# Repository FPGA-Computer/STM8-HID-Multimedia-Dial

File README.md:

# STM8 HID Multimedia Dial

This is a USB HID with a rotatory encoder. This is used to supplement old keyboard layouts by providing a more natural alternative.

Details: https://hw-by-design.blogspot.com/2018/07/hid-multimedia-dial.html

This is a port of my [HID Dial project](https://github.com/FPGA-Computer/HID-Multimedia-Dial) (ATMega8) to STM8S003 using STM8 VUSB library.

# STM8 VUSB

The firmware only USB stack is an unofficial fork from STM8S-VUSB-KEYBOARD at https://github.com/BBS215/STM8S-VUSB-KEYBOARD

- Works with current special edition of Cosmic C (4.4.10) and current version of STVD (4.3.12)

- USB stack logic is modified for this tech demo. HID is now working.

- Code reformatted/refractored.  Using my own IRQ files for STM8S003 for a much cleaner organization. Some code logic changed.

- No longer need a separate GPIO for the 1.5K pull up to connect/disconnect USB.  See schematic.

- Device library calls have been changed to bare metal to minimized dependancy and reduce code size.  stm8s_flash.c is the only library needed.

Note: 

The USB stack calibrates the HSI clock while connected to the PC. The calibration is store in EEPROM. It can take a couple of minutes the first time before it functions correctly.

Timer 1 is used by the USB stack for filtering and interrupt. It is not actually used for counting.

Install a 10K into R1 and 3 0.1uF capacitors to the Rotary Encoder module (made in China).

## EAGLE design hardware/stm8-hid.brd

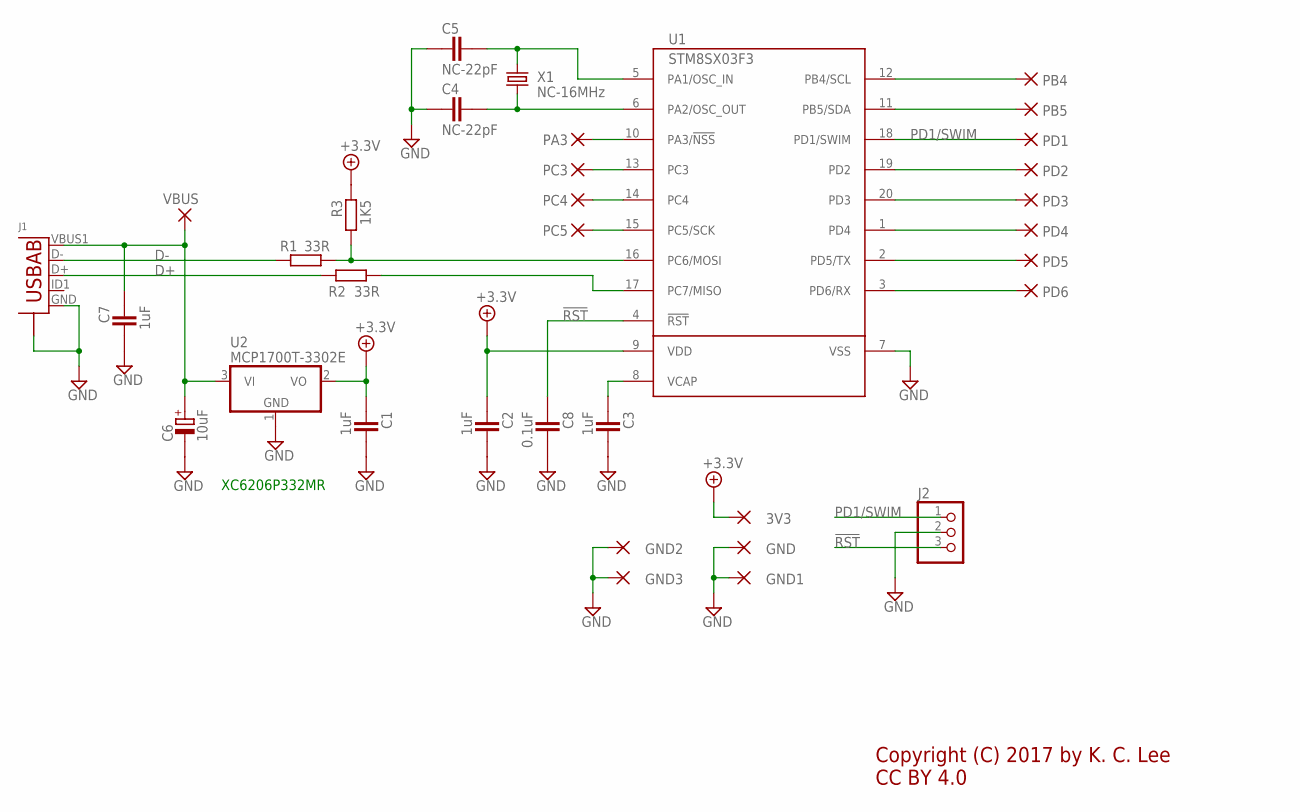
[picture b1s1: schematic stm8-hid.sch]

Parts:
3V3: SMD2; SMD1,27-2,54
C1, C2, C3: 1uF; CAPC1608X92N; PARTNO 1uF X7R 0603
C4, C5: NC-22pF; CAPC1608X92N; PARTNO 22pF 0603
C6: 10uF; CAPMP6032X280N; PARTNO 1uF X7R 0603
C7: 1uF; CAPC1608X92N; PARTNO NC 0805
C8: 0.1uF; CAPC1608X92N; PARTNO 1uF X7R 0603
GND, GND1, GND2, GND3: SMD2; SMD1,27-2,54
J1: USB-ABBG-ORG; USB-AB-MICRO-SMD_V03_SMT
J2: PINHD-1X3_2.54; 1X03
PA3: SMD2; SMD1,27-2,54
PB4, PB5: SMD2; SMD1,27-2,54
PC3, PC4, PC5: SMD2; SMD1,27-2,54
PD1, PD2, PD3, PD4, PD5, PD6: SMD2; SMD1,27-2,54
R1, R2: 33R; RESC1608X55N; PARTNO 47R 0603
R3: 1K5; RESC1608X55N; PARTNO 1K5 0603
U1: STM8SX03F3; TSSOP20
U2: MCP1700T-3302E; SOT95P280X135-3N; PARTNO MCP1700T-3302E/TT
VBUS: SMD2; SMD1,27-2,54; PARTNO Breakout
X1: NC-16MHz; TC38H; PARTNO 16MHz Crystal TC26

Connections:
!RST: C8.1, J2.3, U1.4 (!RST)
+3.3V: 3V3.1, C1.1, C2.1, R3.1, U1.9 (VDD), U2.2 (VO)
D+: J1.D+, R2.1
D-: J1.D-, R1.1
GND: C1.2, C2.2, C3.2, C4.1, C5.1, C6.-, C7.2, C8.2, GND.1, GND1.1, GND2.1, GND3.1, J1.GND, J1.S1 (S), J1.S2 (S), J1.S3 (S), J1.S4 (S), J2.2, U1.7 (VSS), U2.1 (GND)
unnamed: C3.1, U1.8 (VCAP)
unnamed: R2.2, U1.17 (PC7/MISO)
unnamed: R1.2, R3.2, U1.16 (PC6/MOSI)
unnamed: C4.2, U1.6 (PA2/OSC_OUT), X1.2
unnamed: C5.2, U1.5 (PA1/OSC_IN), X1.1
unnamed: PC5.1, U1.15 (PC5/SCK)
unnamed: PC4.1, U1.14 (PC4)
unnamed: PC3.1, U1.13 (PC3)
unnamed: PB4.1, U1.12 (PB4/SCL)
unnamed: PB5.1, U1.11 (PB5/SDA)
unnamed: PD2.1, U1.19 (PD2)
unnamed: PD3.1, U1.20 (PD3)
unnamed: PD4.1, U1.1 (PD4)
unnamed: PD5.1, U1.2 (PD5/TX)
unnamed: PD6.1, U1.3 (PD6/RX)
unnamed: PA3.1, U1.10 (PA3/!NSS)
PD1/SWIM: J2.1, PD1.1, U1.18 (PD1/SWIM)
VBUS: C6.+, C7.1, J1.VBUS1 (VBUS), U2.3 (VI), VBUS.1

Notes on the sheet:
Copyright (C) 2017 by K. C. Lee CC BY 4.0
XC6206P332MR

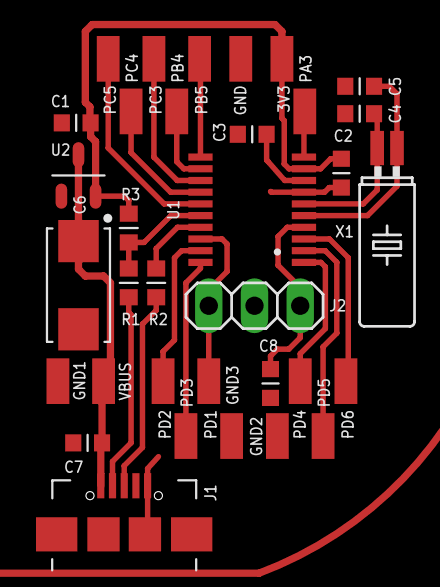
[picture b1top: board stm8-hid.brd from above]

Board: 2 copper layers, 34 parts (0 on the bottom side), 23 nets.

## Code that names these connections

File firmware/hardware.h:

/*
 * hardware.h
 *
 * Created: October 31, 2019, 12:33:01 PM
 *  Author: K. C. Lee
 * Copyright (c) 2019 by K. C. Lee
 
 This program is free software: you can redistribute it and/or modify
 it under the terms of the GNU General Public License as published by
 the Free Software Foundation, either version 3 of the License, or
 (at your option) any later version.

 This program is distributed in the hope that it will be useful,
 but WITHOUT ANY WARRANTY; without even the implied warranty of
 MERCHANTABILITY or FITNESS FOR A PARTICULAR PURPOSE.  See the
 GNU General Public License for more details.

 You should have received a copy of the GNU General Public License
 along with this program.

 If not, see http://www.gnu.org/licenses/gpl-3.0.en.html 
 */ 

#ifndef __CSMC__
#define __CSMC__
#endif
#ifndef STM8S003
#define STM8S003
#endif

#ifndef HARDWARE_H_
#define HARDWARE_H_

#include "stm8s.h"
#include <stdio.h>

// STM8S003F3P6
enum _PA { PA1=0x02, PA2=0x04, PA3=0x08 };
enum _PB { PB4=0x10, PB5=0x20 };
enum _PC { PC3=0x08, PC4=0x10, PC5=0x20, PC6=0x40, PC7=0x80 };
enum _PD { PD1=0x02, PD2=0x04, PD3=0x08, PD4=0x10, PD5=0x20, PD6=0x40 };

#define GPIO(X)					((GPIO_TypeDef *)(X))

#define CPU_CLOCK				16000000UL
#define EE_Addr					0x4000

enum _OPT2 { AFR0 = 0x01, AFR1=0x02, AFR2=0x04, AFR3=0x08, AFR4=0x10, AFR5=0x20, AFR6=0x40, AFR7 = 0x80 };
enum _OPT3 { HSITRIM = 0x10, LSI_EN = 0x08, IWDG_HW = 0x04, WWDG_HW = 0x02, WWDG_HALT = 0x01 };

#define FLASH_RASS_KEY1 ((uint8_t)0x56) /*!< First RASS key */
#define FLASH_RASS_KEY2 ((uint8_t)0xAE)

#define TIM4_PRSC				7
#define TIM4_FREQ				500
#define TIM4_Slow				100
#define TIM4_RELOAD			(CPU_CLOCK/(1<<TIM4_PRSC)/TIM4_FREQ)
#define TIM4_CNTMAX			(TIM4_FREQ/TIM4_Slow)

#define LED_R_PORT			GPIOD
#define LED_R						PD1
#define LED_G_PORT			GPIOB
#define LED_G						PB5
#define LED_B_PORT			GPIOB
#define LED_B						PB4

enum _LED
{
	LED_OFF = 0x00,	LED_RED = 0x01, LED_GREEN = 0x02, LED_BLUE = 0x04,
	LED_YELLOW = LED_RED|LED_GREEN, 
	LED_MAGENTA = LED_RED|LED_BLUE,
	LED_AQUA = LED_GREEN|LED_BLUE, 
	LED_WHITE = LED_RED|LED_GREEN|LED_BLUE
};

#define ENC_PORT				GPIOC
#define ENC_CLK					PC5
#define ENC_DIR					PC4
#define ENC_SW_PORT			GPIOC
#define ENC_SW					PC3

#define EXTI_CR1				0x30

extern volatile uint8_t TIM4_Update_Flag;


// Delays in us.  The delay has been calibrated for 16MHz
// Maximum delay is about 100ms (16-bit)

#define DELAY_TWEAK			0.63
#define US_DELAY(X)			((uint16_t)(X*DELAY_TWEAK))

// Switch status is a shift register that shift left every 16.38ms
#define SW_RISING_EDGE        0x07      // 00000111  <- turned high for 49ms 
#define SW_FALLING_EDGE       0xf8      // 11111000  <- turned low for 49ms 
#define SW_EDGE_MASK          0x0f
#define SW_DEBOUNCE_MASK      0x03

#define SW_AT_MAKE            ((Switch_Status & SW_EDGE_MASK) == (SW_FALLING_EDGE & SW_EDGE_MASK))
#define SW_AT_BREAK           ((Switch_Status & SW_EDGE_MASK) == (SW_RISING_EDGE & SW_EDGE_MASK))
#define SW_MAKE               ((Switch_Status & SW_DEBOUNCE_MASK) == (SW_FALLING_EDGE & SW_DEBOUNCE_MASK))
#define SW_BREAK              ((Switch_Status & SW_DEBOUNCE_MASK) == (SW_RISING_EDGE & SW_DEBOUNCE_MASK))

#define ms_TO_TICKS(X)				((X)/10)

#define TIMER_DBL_BREAK       ms_TO_TICKS(250)
#define TIMER_CLICK_MAKE		  ms_TO_TICKS(150)
#define TIMER_LONG            ms_TO_TICKS(400)

enum SW_STATE
{
  SW_NONE, SW_PRESS, SW_DBL_BREAK, SW_DBL_CLICK, SW_HOLD, SW_BREAK_WAIT
 };

enum ENC_STATES
{
  ENC_VOLUME, ENC_PLAYCTRL
 };

#define ENC_LAST  ENC_PLAYCTRL
#define ENC_FIRST ENC_VOLUME 

#define REPORT_SIZE		    2

enum REPORT_ID
{
  ID_CONSUMER = 0x01
 };

#define ENC_LAST  ENC_PLAYCTRL
#define ENC_FIRST ENC_VOLUME 

enum EndPoint
{
	EP0, EP1
};

enum REPORT_STATE
{
  REPORT_RDY, REPORT_CMD_RELEASE, REPORT_CMD
 };

enum REPORT_BITMAP
{
  Cmd_Next_Track =0x01, Cmd_Prev_Track = 0x02, Cmd_Stop = 0x04, Cmd_Play_Pause = 0x08, 
  Cmd_Mute = 0x10, Cmd_Volume_Up = 0x20, Cmd_Volume_Down = 0x40
 };

void Init_Hardware(void);
void RESET_CHIP(void);
void Check_OPTION_BYTE(void);
void TIM4_Init(void);
void Delay(uint16_t t);
void LED(uint8_t Colour);
void Encoder_Init(void);
void Encoder_Switch_Task(void);
void Encoder_Task(void);
void HID_Task(void);
void FLASH_Data_lock(uint8_t lock);
void FLASH_Wait(void);
#endif

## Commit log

2021-03-04 fix long wait for USB device recognization
2021-03-08 Removed library - smaller code
2021-03-19 keep files sync with dev
